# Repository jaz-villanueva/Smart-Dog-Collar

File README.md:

# 🐕 DIY Smart Dog Collar: Real-Time Mood Detection + AI Translation

A one-month vlog project building a wearable dog mood detector using an ESP32, a motion sensor, a microphone, and machine learning. The collar guesses your dog's mood and "says" it as a simple English phrase.

**Status:** In Development (1-Month Vlog Sprint)  
**Timeline:** October 2026  
**Deliverable:** YouTube vlog + working prototype + open-source code

---

## 🎯 Project Overview

- **Wearable hardware:** Seeed XIAO nRF52840 Sense (motion sensor, microphone, Bluetooth and charger on one 21 × 18 mm board) with a 100–150 mAh LiPo, about 8–11 g in total. See [`hardware/WEARABLE_BUILD.md`](hardware/WEARABLE_BUILD.md).
- **Bench hardware:** ESP32 + MPU6050 (motion) + INMP441 (microphone) on a breadboard, for development
- **Cage camera (recommended):** the only source of where he is. It tracks his position, outline and movement in the cage, and lets you label recordings from video afterwards. See [`docs/CAMERA.md`](docs/CAMERA.md).
- **Firmware:** Arduino C++, binary BLE packets with 50 Hz motion and a 12-band sound spectrum at 25 Hz
- **ML:** Random Forest classifier on 8-second windows of motion, sound, location, heart rate and context
- **Live:** a laptop script that runs the model and speaks the phrase, staying quiet when it is not sure
- **App:** TinyTalk, a web app that installs on a phone, connects to the collar, can use the phone as the cage camera, records labelled data and speaks the phrases. A first version; see [`app/`](app/).
- **Ground truth:** the mood you type into the data logger while watching your dog

**Mood Classes:** Playful, Sleepy, Hungry, Potty, Sad, Lonely, Anxious, Alert, Content, Stressed

The list and the phrases for each mood live in [`ml/moods.json`](ml/moods.json). Edit that one file to add, remove or reword them. Which sensor, signal and feature stands behind each phrase is in [`docs/MOODS.md`](docs/MOODS.md).

Shopping list, with Shopee and Lazada search links: [`docs/PH_SHOPPING_LIST.md`](docs/PH_SHOPPING_LIST.md).

### Carrier board (optional)

A small two-layer board the XIAO solders onto, holding the switch and battery. It passes KiCad's design rule check but has not been fabricated yet. Details, Gerbers and assembly steps are in [`hardware/pcb/`](hardware/pcb/).

Assembled, from above and below. The XIAO, switch and battery are simplified block models, so sizes are nominal and the positions of parts on the XIAO are approximate:

The bare board, top and bottom:

### Housing

A two-part printed case for the carrier-board build, with rounded edges, a USB-C opening, a switch slot and a microphone hole. It is modelled but not yet printed. Files and print settings are in [`hardware/enclosure/`](hardware/enclosure/).

These are renders of the 3D model, not photos:

### What is built and what is not

| Part | State |
|------|-------|
| ESP32 bench firmware | Written. Not yet compiled or run on hardware. |
| XIAO wearable firmware | Written. Not yet compiled or run on hardware. |
| Wearable hardware | Designed. Not yet built; weight and battery life are estimates. |
| Carrier PCB (optional) | Designed; passes KiCad's design rule check. Not yet fabricated. See [`hardware/pcb/`](hardware/pcb/). |
| Data logger | Written. Packet decoding, heart-rate decoding and CSV output tested with synthetic packets; not yet run against a real collar or strap. |
| Trainer | Written. Runs end to end on synthetic data; no real dog data yet. |
| Live prediction | Written. Tested by replaying synthetic packets; not yet run against a real collar. |
| Cage camera, unattended recording, video labelling | Written. Tested on a synthetic video; not yet run on a real camera or dog. |
| Tail, ear and posture tracking (pose model) | Not started. |
| Housing for the carrier-board build | Modelled; not yet printed. See [`hardware/enclosure/`](hardware/enclosure/). |
| Starter dataset and model | **Synthetic**, for running the scripts only; says nothing about a real dog. See [`data/starter/`](data/starter/). |
| TinyTalk web app | First version, with phone-as-camera and recording. Demo mode, the model arithmetic and the camera tracker (on made-up pictures) tested; not yet used with a real collar, cage or dog. See [`app/`](app/). |
| On-collar speaker, real dog dataset | Not started. |

---

## 📁 Repository Structure

```
dog-mood-collar-vlog/
├── firmware/
│   ├── dog_collar_xiao/              # Wearable: XIAO nRF52840 Sense
│   └── dog_collar_firmware/          # Bench prototype: ESP32 + breakouts
├── ml/
│   ├── moods.json                    # Mood classes + spoken phrases
│   ├── collar.py                     # BLE connection + packet decoding (shared)
│   ├── features.py                   # Window features (shared)
│   ├── ble_data_logger.py            # Record sensor data + label moods
│   ├── train_mood_model.py           # Train and test the classifier
│   ├── live_predict.py               # Say his mood live
│   ├── make_voice_clips.py           # Record the phrases as sound clips for the app
│   ├── prepare_voice_clips.py        # Trim, level and pitch clips recorded elsewhere
│   ├── export_app_model.py           # Export a trained model for the web app
│   ├── make_starter_dataset.py       # Writes the synthetic starter data
│   ├── starter_model/                # Model trained on the synthetic data
│   ├── camera.py                     # Cage camera tracker
│   ├── label_video.py                # Label a recording from its video
│   └── requirements.txt
├── hardware/
│   ├── WEARABLE_BUILD.md             # The light version he wears
│   ├── pcb/                          # Optional carrier board (KiCad, Gerbers, renders)
│   ├── enclosure/                    # Printable housing for the carrier board (STL, STEP)
│   ├── BOM.csv                       # Bench prototype bill of materials
│   └── WIRING_REFERENCE.txt          # Bench prototype connections and checks
├── data/                             # Your recordings (git-ignored)
│   └── starter/                      # Synthetic starter dataset
├── app/                              # TinyTalk web app (installable, runs the model on the phone)
└── docs/
    ├── PH_SHOPPING_LIST.md           # What to buy, and what not to
    ├── MOODS.md                      # Sensor, signal, features and phrase for each mood
    ├── CAMERA.md                     # Cage camera setup and labelling from video
    ├── images/                       # Drawings
    └── ...                           # Older checklists*
```

*\*`BUILD_CHECKLIST.md`, `TROUBLESHOOTING.md` and `FUTURE_IMPROVEMENTS.md` still describe the original four-sensor design and need updating.*

---

## 🚀 Quick Start

### 1. Hardware
**To put it on the dog,** build the wearable from [`hardware/WEARABLE_BUILD.md`](hardware/WEARABLE_BUILD.md) and skip to step 2. The steps below are for the ESP32 bench prototype, which is too heavy for a small dog.

1. Wire the breadboard from `hardware/WIRING_REFERENCE.txt`. **Read the power section first:** the battery goes on the TP4056 `B+`/`B-` pads, never `IN+`/`IN-`.
2. In Arduino IDE, install ESP32 board support and the **Adafruit MPU6050** library.
3. Flash `firmware/dog_collar_firmware/dog_collar_firmware.ino`.
4. Open the Serial Monitor at 115200 baud and run the bench checks in the wiring reference.

### 2. Data collection
```bash
pip install -r ml/requirements.txt
```
```bash
python ml/ble_data_logger.py
```
Type a mood (a unique prefix is enough, e.g. `hu` for hungry) to start labelling, `u` to pause. Also tell the logger what the sensors cannot see:

| Command | Meaning |
|---------|---------|
| `fed` | he just ate |
| `went` | he just peed or pooped |
| `away` / `home` | you are leaving him alone / you are back |

**Or record now and label later.** With a camera on his cage, the logger can record everything while you are away, and you label the video afterwards. See [`docs/CAMERA.md`](docs/CAMERA.md).

```bash
python ml/ble_data_logger.py --camera 0 --unattended
```
```bash
python ml/label_video.py
```

### 3. Training
```bash
python ml/train_mood_model.py
```
The model and its confusion matrix go to `ml/trained_models/`.

### 4. Live moods
```bash
python ml/live_predict.py
```
Every 4 seconds it prints the mood for the last 8 seconds, averaged over the last three predictions. When the model is at least 50% confident it speaks one of the phrases through the computer; otherwise it prints "not sure". The `fed`, `went`, `away` and `home` commands work here too. Add `--mute` to print without speaking.

### Optional: heart rate (larger dogs only)
A chest strap is too big and heavy for a teacup puppy; skip this section for him.

A dog's heart rate and its beat-to-beat variability change with excitement and stress, which motion and sound cannot always show. An ECG chest strap that speaks the standard Bluetooth Heart Rate profile (for example a Polar H10) can be recorded alongside the collar:

```bash
python ml/ble_data_logger.py --hr Polar
```
```bash
python ml/live_predict.py --hr Polar
```

Wet the electrodes or use electrode gel, and part the fur so they touch skin behind the front legs. Readings are most reliable while he is still. This path is untested on a real dog; check that `?` in the logger shows a plausible heart rate before recording. A model trained with the strap needs the strap at prediction time.

---

## 🏷️ Labelling moods well

Your labels are the ground truth, so the model can only be as good as they are.

- **Label when you are sure.** Pause (`u`) whenever you are not.
- **Anchor each mood to a situation you can recognise:**

| Mood | Good moments to record |
|------|------------------------|
| Playful | Play bows, bringing a toy, zoomies |
| Sleepy | Yawning, curling up, settling in his bed |
| Hungry | Before a late meal: hovering at the bowl, following you to the kitchen |
| Potty | Hours since his last break: waiting at the door, circling, sniffing |
| Sad | Low, slow, withdrawn; ignoring toys and people |
| Lonely | Alone after you leave: whining, howling, waiting by the door |
| Anxious | Pacing, panting, trembling (thunder, fireworks, the vet) |
| Alert | Frozen and focused, barking at a sound or visitor |
| Content | Relaxed while being petted or resting near you |
| Stressed | Overwhelmed: too many people, loud noise, being handled |

- **Record every mood on several separate occasions**, at least 5 and ideally 10+, each a minute or more. The trainer tests on occasions it never trained on and skips any mood with fewer than 2.
- **Lonely needs you to be gone.** Record unattended with the cage camera and label the video afterwards, or start the label, type `away`, and leave the laptop in BLE range.

---

## 📋 Hardware BOM

| Component | Model | Price* | Notes |
|-----------|-------|--------|-------|
| Microcontroller | ESP32-WROOM-32 | — | Already owned |
| IMU | MPU6050 | ₱250 | 6-axis accel + gyro, I2C |
| Microphone | INMP441 | ₱150 | I2S, barks and whines |
| LiPo Battery | 1000mAh 3.7V | ₱300 | With protection circuit |
| Charging | TP4056 with protection | ₱100 | 6-pad module |
| Regulator | HT7333 / MCP1700-3302 | ₱50 | Battery → 3.3V |
| USB-C Port | Breakout | ₱100 | Charging |
| Heart rate (optional) | Polar H10 or other BLE ECG chest strap | not priced | Connects to the laptop, not the collar |

**Total new purchases (PH):** about ₱1,850 including perfboard, filament and straps.

*\*Budget estimates. See `hardware/BOM.csv` for the full list.*

The first design also had a MAX30102 heart-rate sensor and an MLX90614 IR thermometer. Both were dropped: the MAX30102 is designed for bare human skin held still, and the MLX90614 would read the fur surface, not body temperature. Heart rate now comes from the optional chest strap instead.

An on-collar speaker is planned for later. It needs an I2S amplifier such as the MAX98357A; the PAM8403 is an analog amplifier and cannot take I2S directly.

---

## 📊 Targets

| Metric | Target | Achieved |
|--------|--------|----------|
| Accuracy on held-out sessions | Clearly above the "most common mood" baseline the trainer prints | — |
| BLE Range | >10m | — |
| Battery Life | 6–8 hrs | — |
| Accuracy when the model is confident enough to speak | Higher than the overall figure; the trainer prints both | — |
| Mood Latency | 8–16 sec (8-second window, smoothed over three predictions) | — |
| Vlog Duration | 15–20 min | — |

---

## ⚠️ Known Limitations

- **The model learns your reading of your dog.** There is no instrument that measures a dog's mood, so "accuracy" means agreement with your labels.
- **Hungry and potty lean on context.** They are predicted mostly from the time since you typed `fed` or `went`, helped by where the cage camera sees him, so they only work while you keep logging those events. Run the trainer with `--no-context` to see how far motion and sound alone get.
- **A model belongs to one device.** The ESP32 prototype and the XIAO wearable have different microphones and motion sensors. Record the training data on the device he will wear.
- **Similar moods will be confused.** Expect sad/sleepy/content and anxious/stressed/alert to blur; the confusion matrix shows which.
- **One dog.** A model trained on your dog will not transfer to another.
- **No view of his tail or ears.** They carry much of a dog's mood. The cage camera sees only his outline, position and movement; tracking body parts needs an animal pose model, which is the next step beyond this design.
- **The laptop must stay in BLE range** (about 10 m) for both recording and live prediction.
- The housing is 3D-printed and not waterproof. Do not leave the collar on an unsupervised dog, and never charge it while he is wearing it.

---

## 🎥 Vlog Narrative

**Hook (0:00–0:15):** "I built an AI collar that translates my dog's mood to English"

**Build (0:15–8:00):** Assembly, soldering montage, code walkthrough, data collection time-lapse

**Training (8:00–12:00):** Model training, feature importance, confusion matrix

**Demo (12:00–18:00):** Real-time predictions on actual dog behavior

**Closeout (18:00–20:00):** Learnings, challenges, future improvements

---

## 🤝 Contributing

This is a vlog/learning project, but if you:
- Build this and find improvements
- Adapt it for other animals
- Improve the ML model
- Add new features

Feel free to fork and share your results!

---

## 📝 License

MIT License — See LICENSE file for details

Free to use, modify, and share for personal/educational projects.

---

## 📚 References

- [MPU6050 Datasheet](https://invensense.tdk.com/wp-content/uploads/2015/02/MPU-6000-Datasheet1.pdf)
- [INMP441 Datasheet](https://invensense.tdk.com/wp-content/uploads/2015/02/INMP441.pdf)
- [Random Forest Classifier](https://scikit-learn.org/stable/modules/generated/sklearn.ensemble.RandomForestClassifier.html)
- [StratifiedGroupKFold](https://scikit-learn.org/stable/modules/generated/sklearn.model_selection.StratifiedGroupKFold.html)
- [Bleak (Python BLE)](https://bleak.readthedocs.io/)

---

## 👤 Author

Built by **Jaz Villanueva** (DLSU Computer Engineering)

---

**Last Updated:** October 2026 | **Status:** 🚀 In Progress

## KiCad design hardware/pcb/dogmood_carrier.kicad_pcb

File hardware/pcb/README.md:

# Carrier Board for the XIAO nRF52840 Sense

A small two-layer board that the XIAO solders onto. It replaces the loose battery wires and switch of the hand-wired build with something tidier and sturdier.

The XIAO, switch and battery above are simplified block models from [`models/`](models/), for illustration only: sizes are nominal and the positions of parts on the XIAO are approximate. The bare board:

It is deliberately **not** a from-scratch board with its own radio chip. The XIAO already carries the processor, antenna, motion sensor, microphone and charger, tested and certified by its maker. This board only adds what the XIAO lacks.

## Status

| Check | Result |
|-------|--------|
| KiCad design rule check (KiCad 10.0.4) | 0 violations, 0 unconnected items; see [`drc_report.txt`](drc_report.txt) |
| Fabricated | **No** |
| Assembled and powered | **No** |
| Schematic file | None. The board is generated from [`generate_carrier.py`](generate_carrier.py), which lists every pad, net and track. The net table below is the schematic. |

The rule check confirms the copper matches the intended connections and meets clearance rules. It cannot confirm that the intended connections are right, or that the XIAO's pads are where the footprint says. **Order a small batch and run the checks under "Before you solder the battery" on the first board.**

## What it does

| Feature | Detail |
|---------|--------|
| Size | 28.6 × 21.9 mm, 0.8 mm thick, about 1 g bare (estimate) |
| Battery | Two plated holes for the LiPo's wires, marked `+` and `−` |
| Switch | Footprint for an SS12D00-type slide switch in the battery's positive lead |
| Battery pads | Plated holes under the XIAO's `BAT+`/`BAT−` pads, soldered from the back |
| Expansion | Four holes for a future I2C sensor: GND, 3V3, SCL, SDA |
| Antenna | No copper under the XIAO's antenna end |

## Connections

| Net | From | To |
|-----|------|----|
| `BAT_PLUS` | Battery `+` hole | Switch middle pin |
| `VBAT_SWITCHED` | Switch pin at the `ON` end | XIAO underside battery pad (pad 19, `VBAT`) |
| `GND` | Battery `−` hole, XIAO `GND` pin, XIAO underside pad 20, expansion `G` | Ground plane on the back |
| `+3V3` | XIAO `3V3` pin | Expansion `3` |
| `SDA` | XIAO `D4` | Expansion `A` |
| `SCL` | XIAO `D5` | Expansion `L` |

All other XIAO pins are soldered for mechanical strength only.

## Parts

| Ref | Part | Notes |
|-----|------|-------|
| U1 | Seeed XIAO nRF52840 Sense | Without header pins |
| SW1 | SS12D00 slide switch, 3 pins in a row, about 2.5 mm pitch | Common on Shopee as "SS12D00G3" |
| J1 | LiPo cell, 100–150 mAh, protected | Bare wire leads |
| J2 | Not fitted | For a future I2C sensor |

## Ordering

Upload the files in [`gerbers/`](gerbers/) as a zip to a board maker such as JLCPCB or PCBWay.

- Layers: 2
- Thickness: **0.8 mm** (lighter than the usual 1.6 mm)
- Everything else: defaults

No assembly service is needed; every part is hand-soldered.

## Assembly

1. **Switch.** Fit SW1 on the top, solder its three pins from the back, and trim them flush.
2. **XIAO.** Lay it on the top with its USB connector toward the edge with the four expansion holes, and its edge pads over the fourteen large pads. Tack one corner, check the alignment on both sides, then solder all fourteen.
3. **Battery pads.** Turn the board over. Feed solder into the two oval holes under the XIAO until it wets the XIAO's pad above each hole.
4. Stop here and run the checks below.
5. **Battery.** Solder the red lead into `+` and the black lead into `−`. Route the wires away from the end of the board with no copper, where the antenna is.

### Before you solder the battery

Use a multimeter on continuity or resistance:

- [ ] The `−` battery hole connects to the XIAO's `GND` pin.
- [ ] The `+` battery hole does **not** connect to `GND` with the switch in either position.
- [ ] With the switch at `ON`, the `+` hole connects to the oval hole **further from** the USB connector. With the switch at `OFF`, it does not.
- [ ] The oval hole **nearer** the USB connector connects to `GND`.

Then plug in USB with no battery: the XIAO should start normally. Only then solder the battery, and check its polarity with the multimeter first. A reversed LiPo can destroy the board and overheat.

If the `ON`/`OFF` labels turn out to be the wrong way round for your switch, that is harmless; just note it.

## Changing the design

Edit `generate_carrier.py`, then regenerate, fill the ground plane, and re-run the rule check:

```bash
"C:\Program Files\KiCad\10.0\bin\python.exe" generate_carrier.py
```
```bash
"C:\Program Files\KiCad\10.0\bin\kicad-cli.exe" pcb drc --refill-zones --save-board --severity-all -o drc_report.txt dogmood_carrier.kicad_pcb
```

The board also opens directly in KiCad's PCB editor.

## Source of the XIAO dimensions

Pad positions and pin names come from Seeed Studio's published KiCad library, footprint and symbol `XIAO-nRF52840-SMD` (https://github.com/Seeed-Studio/OPL_Kicad_Library, retrieved 2026-10-01). The footprint here is drawn from those dimensions, with the two battery pads changed from surface pads to plated holes so they can be soldered by hand.

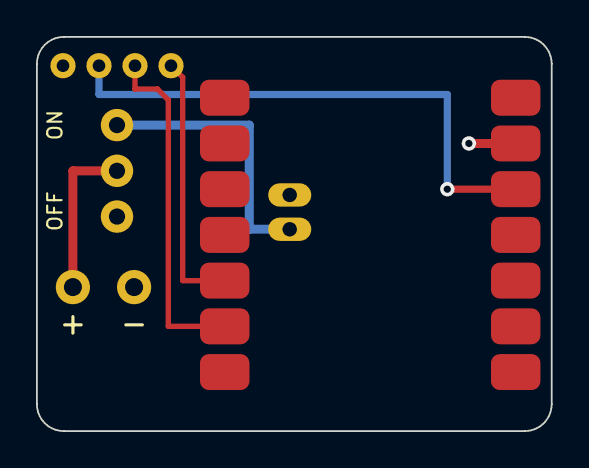
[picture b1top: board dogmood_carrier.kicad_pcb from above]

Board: 2 copper layers, 28.6 x 21.9 mm, 4 parts (0 on the bottom side), 6 nets.

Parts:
J1: LiPo battery wires
J2: I2C expansion pads
SW1: SS12D00 slide switch
U1: XIAO nRF52840 Sense

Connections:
+3V3: J2.2, U1.12
BAT_PLUS: J1.1, SW1.2
GND: J1.2, J2.1, U1.13, U1.20
SCL: J2.3, U1.6
SDA: J2.4, U1.5
VBAT_SWITCHED: SW1.1, U1.19
